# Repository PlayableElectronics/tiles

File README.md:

# PE - Tiles
Modular controller platform for midi, osc and more...

Connecting accessible components, well known standards (Grove, OSC, Midi) into easy and working systems tailored to your personal needs.

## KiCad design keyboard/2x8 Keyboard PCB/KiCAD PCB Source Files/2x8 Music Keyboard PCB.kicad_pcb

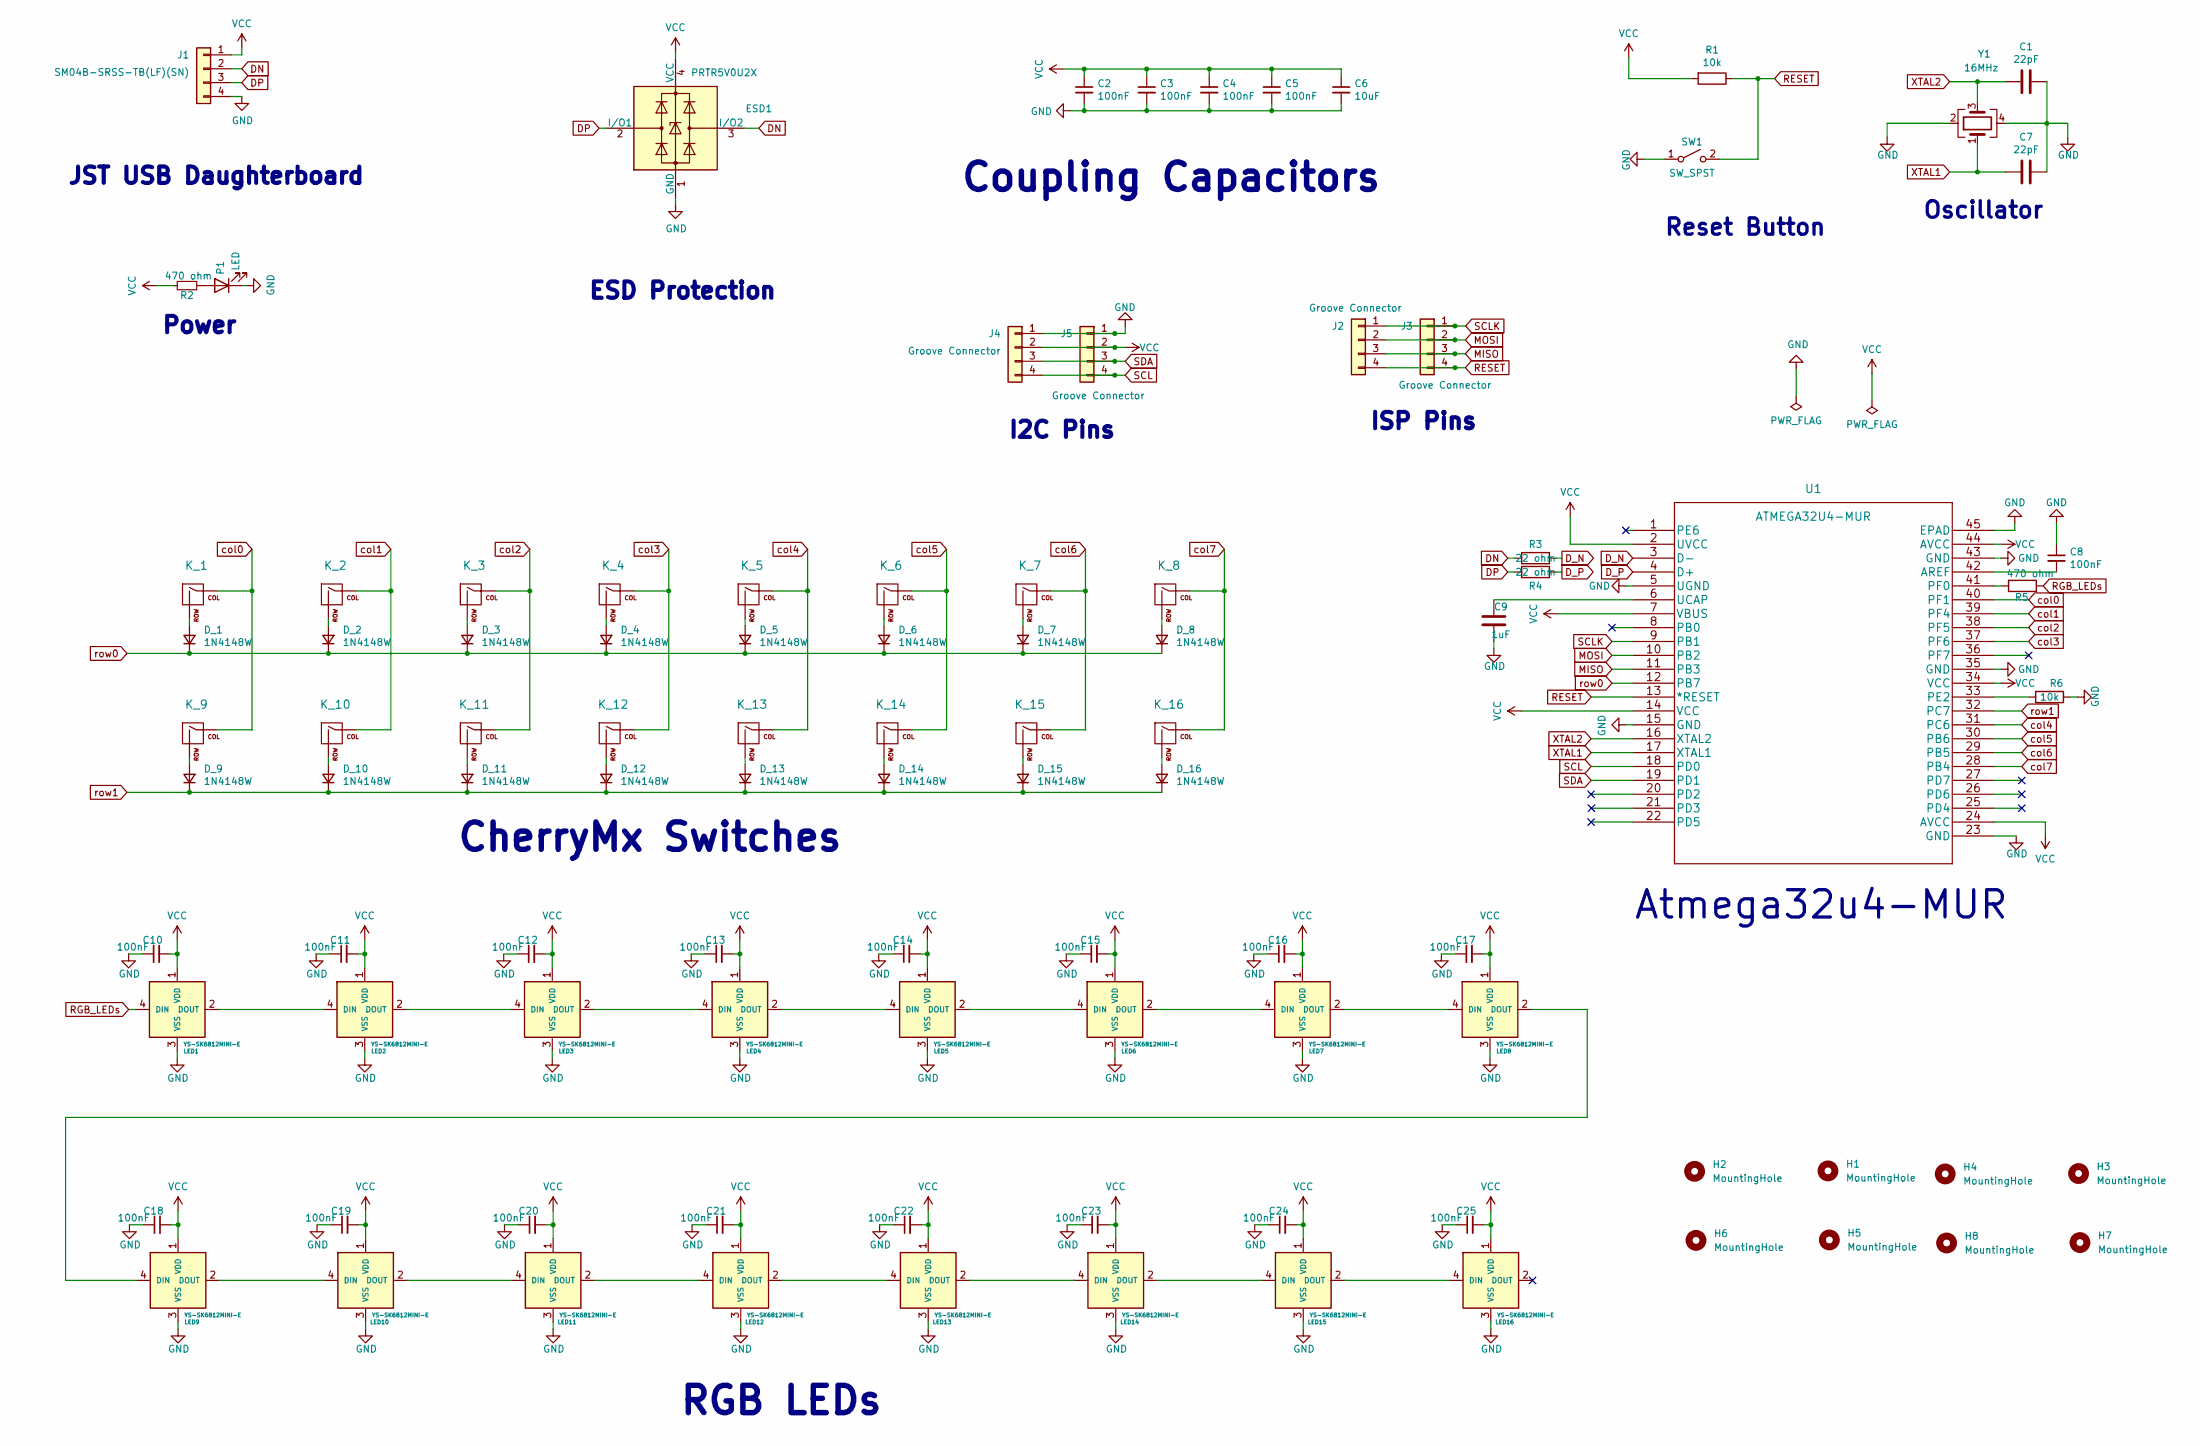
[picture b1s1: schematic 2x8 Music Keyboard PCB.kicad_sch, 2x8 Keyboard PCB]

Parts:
C1, C7: 22pF; C_0603_1608Metric
C2, C3, C4, C5, C8, C10, C11, C12, C13, C14, C15, C16, C17, C18, C19, C20, C21, C22, C23, C24, C25: 100nF; C_0603_1608Metric
C6: 10uF; C_0603_1608Metric
C9: 1uF; C_0603_1608Metric; LCSC Part # C28323
D_1, D_2, D_3, D_4, D_5, D_6, D_7, D_8, D_9, D_10, D_11, D_12, D_13, D_14, D_15, D_16: 1N4148W; D_SOD-123
ESD1: PRTR5V0U2X; LCSC C2827688
H1, H2, H3, H4, H5, H6, H7, H8: MountingHole; HOLE-3mm
J1: SM04B-SRSS-TB(LF)(SN); JST_SH_SM04B-SRSS-TB_1x04-1MP_P1.00mm_Horizontal
J2, J4: Groove Connector; JST_PH_S4B-PH-SM4-TB_1x04-1MP_P2.00mm_Horizontal
J3, J5: Groove Connector; JST_PH_B4B-PH-K_1x04_P2.00mm_Vertical
K_1, K_2, K_3, K_4, K_5, K_6, K_7, K_8, K_9, K_10, K_11, K_12, K_13, K_14, K_15, K_16: KEYSW-1u; MXOnly-1U-NoLED
LED1, LED2, LED3, LED4, LED5, LED6, LED7, LED8, LED9, LED10, LED11, LED12, LED13, LED14, LED15, LED16: YS-SK6812MINI-E; CRONE-SK6812MINI-E
P1: LED; LED_0603_1608Metric; LCSC C473820
R1, R6: 10k; R_0603_1608Metric; LCSC Part # C17414
R2, R5: 470 ohm; R_0603_1608Metric
R3, R4: 22 ohm; R_0603_1608Metric; LCSC Part # C17561
SW1: SW_SPST; K2-1187SQ-A4SW-06; Manufacturer Part Number K2-1187SQ-A4SW-06
U1: ATMEGA32U4-MUR; ATMEGA32U4-MURr; LCSC Part # C45874
Y1: 16MHz; Crystal_SMD_3225-4Pin_3.2x2.5mm; LCSC Part # C13738

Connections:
DN: ESD1.3 (I/O2), J1.2, R3.2
DP: ESD1.2 (I/O1), J1.3, R4.2
D_N: R3.1, U1.3 (D-)
D_P: R4.1, U1.4 (D+)
GND: C1.1, C2.2, C3.2, C4.2, C5.2, C6.2, C7.1, C8.1, C9.2, C10.1, C11.1, C12.1, C13.1, C14.1, C15.1, C16.1, C17.1, C18.1, C19.1, C20.1, C21.1, C22.1, C23.1, C24.1, C25.1, ESD1.1 (GND), J1.4, J4.1, J5.1, LED1.3 (VSS), LED2.3 (VSS), LED3.3 (VSS), LED4.3 (VSS), LED5.3 (VSS), LED6.3 (VSS), LED7.3 (VSS), LED8.3 (VSS), LED9.3 (VSS), LED10.3 (VSS), LED11.3 (VSS), LED12.3 (VSS), LED13.3 (VSS), LED14.3 (VSS), LED15.3 (VSS), LED16.3 (VSS), P1.1 (K), R6.1, SW1.1 (A), U1.5 (UGND), U1.15 (GND), U1.23 (GND), U1.35 (GND), U1.43 (GND), U1.45 (EPAD), Y1.2, Y1.4
MISO: J2.3, J3.3, U1.11 (PB3)
MOSI: J2.2, J3.2, U1.10 (PB2)
unnamed: C8.2, U1.42 (AREF)
unnamed: C9.1, U1.6 (UCAP)
unnamed: D_1.2 (A), K_1.2 (ROW)
unnamed: D_2.2 (A), K_2.2 (ROW)
unnamed: D_3.2 (A), K_3.2 (ROW)
unnamed: D_4.2 (A), K_4.2 (ROW)
unnamed: D_5.2 (A), K_5.2 (ROW)
unnamed: D_6.2 (A), K_6.2 (ROW)
unnamed: D_7.2 (A), K_7.2 (ROW)
unnamed: D_8.2 (A), K_8.2 (ROW)
unnamed: D_9.2 (A), K_9.2 (ROW)
unnamed: D_10.2 (A), K_10.2 (ROW)
unnamed: D_11.2 (A), K_11.2 (ROW)
unnamed: D_12.2 (A), K_12.2 (ROW)
unnamed: D_13.2 (A), K_13.2 (ROW)
unnamed: D_14.2 (A), K_14.2 (ROW)
unnamed: D_15.2 (A), K_15.2 (ROW)
unnamed: D_16.2 (A), K_16.2 (ROW)
unnamed: LED1.2 (DOUT), LED2.4 (DIN)
unnamed: LED2.2 (DOUT), LED3.4 (DIN)
unnamed: LED3.2 (DOUT), LED4.4 (DIN)
unnamed: LED4.2 (DOUT), LED5.4 (DIN)
unnamed: LED5.2 (DOUT), LED6.4 (DIN)
unnamed: LED6.2 (DOUT), LED7.4 (DIN)
unnamed: LED7.2 (DOUT), LED8.4 (DIN)
unnamed: LED8.2 (DOUT), LED9.4 (DIN)
unnamed: LED10.2 (DOUT), LED11.4 (DIN)
unnamed: LED9.2 (DOUT), LED10.4 (DIN)
unnamed: LED11.2 (DOUT), LED12.4 (DIN)
unnamed: LED12.2 (DOUT), LED13.4 (DIN)
unnamed: LED13.2 (DOUT), LED14.4 (DIN)
unnamed: LED14.2 (DOUT), LED15.4 (DIN)
unnamed: LED15.2 (DOUT), LED16.4 (DIN)
unnamed: P1.2 (A), R2.1
unnamed: R5.2, U1.41 (PF0)
unnamed: R6.2, U1.33 (PE2)
RESET: J2.4, J3.4, R1.1, SW1.2 (B), U1.13 (*RESET)
RGB_LEDs: LED1.4 (DIN), R5.1
SCL: J4.4, J5.4, U1.18 (PD0)
SCLK: J2.1, J3.1, U1.9 (PB1)
SDA: J4.3, J5.3, U1.19 (PD1)
VCC: C2.1, C3.1, C4.1, C5.1, C6.1, C10.2, C11.2, C12.2, C13.2, C14.2, C15.2, C16.2, C17.2, C18.2, C19.2, C20.2, C21.2, C22.2, C23.2, C24.2, C25.2, ESD1.4 (VCC), J1.1, J4.2, J5.2, LED1.1 (VDD), LED2.1 (VDD), LED3.1 (VDD), LED4.1 (VDD), LED5.1 (VDD), LED6.1 (VDD), LED7.1 (VDD), LED8.1 (VDD), LED9.1 (VDD), LED10.1 (VDD), LED11.1 (VDD), LED12.1 (VDD), LED13.1 (VDD), LED14.1 (VDD), LED15.1 (VDD), LED16.1 (VDD), R1.2, R2.2, U1.2 (UVCC), U1.7 (VBUS), U1.14 (VCC), U1.24 (AVCC), U1.34 (VCC), U1.44 (AVCC)
XTAL1: C7.2, U1.17 (XTAL1), Y1.1
XTAL2: C1.2, U1.16 (XTAL2), Y1.3
col0: K_1.1 (COL), K_9.1 (COL), U1.40 (PF1)
col1: K_2.1 (COL), K_10.1 (COL), U1.39 (PF4)
col2: K_3.1 (COL), K_11.1 (COL), U1.38 (PF5)
col3: K_4.1 (COL), K_12.1 (COL), U1.37 (PF6)
col4: K_5.1 (COL), K_13.1 (COL), U1.31 (PC6)
col5: K_6.1 (COL), K_14.1 (COL), U1.30 (PB6)
col6: K_7.1 (COL), K_15.1 (COL), U1.29 (PB5)
col7: K_8.1 (COL), K_16.1 (COL), U1.28 (PB4)
row0: D_1.1 (K), D_2.1 (K), D_3.1 (K), D_4.1 (K), D_5.1 (K), D_6.1 (K), D_7.1 (K), D_8.1 (K), U1.12 (PB7)
row1: D_9.1 (K), D_10.1 (K), D_11.1 (K), D_12.1 (K), D_13.1 (K), D_14.1 (K), D_15.1 (K), D_16.1 (K), U1.32 (PC7)

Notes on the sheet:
Power
RGB LEDs
JST USB Daughterboard
Oscillator
CherryMx Switches
ESD Protection
Coupling Capacitors
Atmega32u4-MUR
ISP Pins
I2C Pins
Reset Button

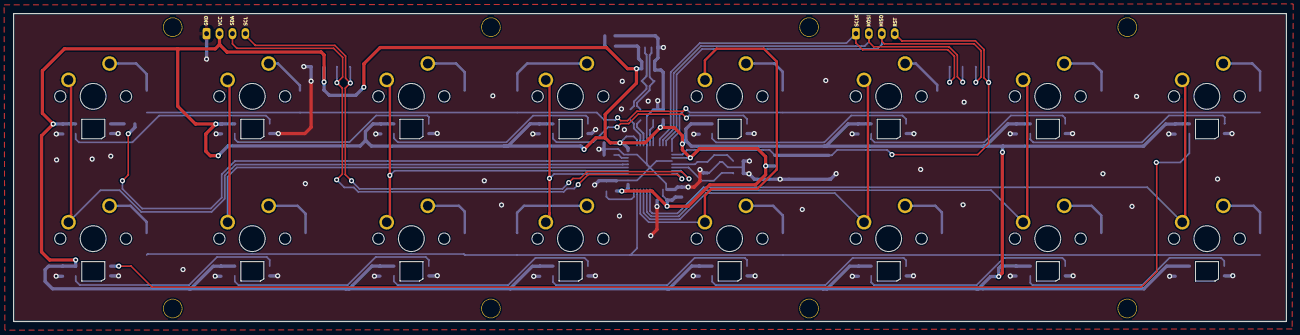
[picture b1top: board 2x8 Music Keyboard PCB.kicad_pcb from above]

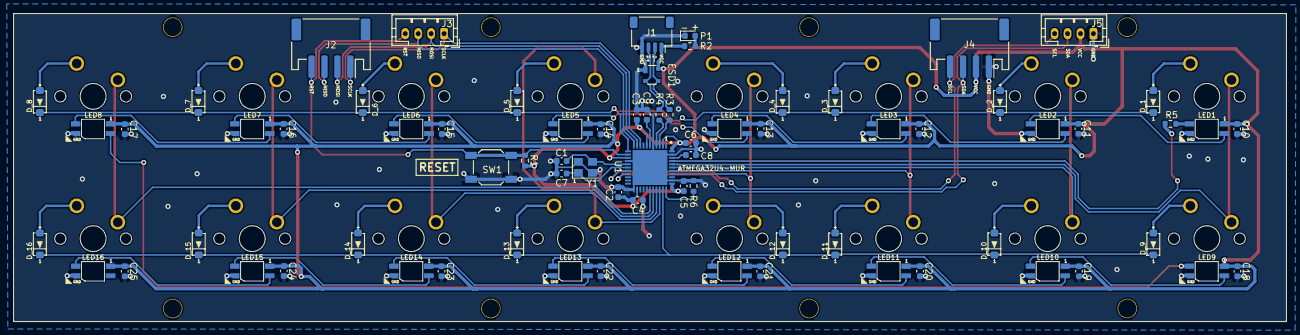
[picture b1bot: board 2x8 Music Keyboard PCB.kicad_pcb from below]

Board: 2 copper layers, 196.8 x 47.6 mm, 97 parts (77 on the bottom side), 61 nets.

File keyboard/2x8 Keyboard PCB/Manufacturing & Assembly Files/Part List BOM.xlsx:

Item | Qty | Reference(s) | Value | Footprint | JLCPCB Part# | Weblink | Column1 | Column2
1 | 2 | C1, C7 | 22pF | Ahsan Libs:C_0603_1608Metric | C1653 | https://lcsc.com/product-detail/Multilayer-Ceramic-Capacitor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
2 | 21 | C2, C3, C4, C5, C8, C10, C11, C12, C13, C14, C15, C16, C17, C18, C19, C20, C21,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 | 100nF | Ahsan Libs:C_0603_1608Metric | C14663 | https://lcsc.com/product-detail/Multilayer-Ceramic-Capacitor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
3 | 1 | C6 | 10uF | Ahsan Libs:C_0603_1608Metric | C15849 | https://lcsc.com/product-detail/Multilayer-Ceramic-Capacitor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
4 | 1 | C9 | 1uF | Ahsan Libs:C_0603_1608Metric | C96446 | https://www.lcsc.com/product-detail/Multilayer-Ceramic-Capac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
5 | 16 | D_1, D_2, D_3, D_4, D_5, D_6, D_7, D_8, D_9, D_10, D_11, D_12, D_13, D_14, D_15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 | 1N4148W | Ahsan Libs:D_SOD-123 | C81598 | https://lcsc.com/product-detail/Switching-Diode_ST-Semtech-1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
6 | 1 | ESD1 | PRTR5V0U2X | Ahsan Libs:PRTR5V0U2X | C2827688 | https://www.lcsc.com/product-detail/ESD-Protection-Devices_T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
7 | 1 | J1 | SM04B-SRSS-TB(LF)(SN) | Ahsan Libs:JST_SH_SM04B-SRSS-TB_1x04-1MP_P1.00mm_Horizontal | C160404 | https://www.lcsc.com/product-detail/Others_JST-Sales-America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
8 | 2 | J2, J4 | Groove Connector | Connector_JST:JST_PH_S4B-PH-SM4-TB_1x04-1MP_P2.00mm_Horizontal | C265289 | https://www.lcsc.com/product-detail/Wire-To-Board-Wire-To-Wi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
9 | 2 | J3, J5 | Groove Connector | Connector_JST:JST_PH_B4B-PH-K_1x04_P2.00mm_Vertical | C131334 | https://www.lcsc.com/product-detail/Wire-To-Board-Wire-To-Wi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
10 | 16 | K_1, K_2, K_3, K_4, K_5, K_6, K_7, K_8, K_9, K_10, K_11, K_12, K_13, K_14, K_15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 | KEYSW-1u | Ahsan Libs:MXOnly-1U-NoLED | C400232 | https://www.lcsc.com/product-detail/Mechanical-Keyboard-Shaf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
11 | 16 | LED1, LED2, LED3, LED4, LED5, LED6, LED7, LED8, LED9, LED10, LED11, LED12, LED1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 | YS-SK6812MINI-E | Ahsan Libs:CRONE-SK6812MINI-E | C5149201 | https://www.lcsc.com/product-detail/Light-Emitting-Diodes-LE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 | https://shop.beekeeb.com/product/sk6812mini-e/ | https://www.adafruit.com/product/4960
12 | 1 | P1 | LED | Ahsan Libs:LED_0603_1608Metric | C72041 | https://lcsc.com/product-detail/Light-Emitting-Diodes-LED_Ev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
13 | 2 | R1, R6 | 10k | Ahsan Libs:R_0603_1608Metric | C25804 | https://lcsc.com/product-detail/Chip-Resistor-Surface-Mount_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
14 | 1 | R2 | 470 ohm | Ahsan Libs:R_0603_1608Metric | C23179 | https://lcsc.com/product-detail/Chip-Resistor-Surface-Mount_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
15 | 2 | R3, R4 | 22 ohm | Ahsan Libs:R_0603_1608Metric | C1203 | https://lcsc.com/product-detail/Chip-Resistor-Surface-Mount_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
16 | 1 | R5 | 470 ohm | Ahsan Libs:R_0603_1608Metric | C23179 | https://lcsc.com/product-detail/Chip-Resistor-Surface-Mount_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
17 | 1 | SW1 | SW_SPST | Ahsan Libs:K2-1187SQ-A4SW-06 | C388295 | https://lcsc.com/product-detail/Tactile-Switches_SHOU-HAN-TS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
18 | 1 | U1 | ATMEGA32U4-MUR | Ahsan Libs:ATMEGA32U4-MURr | C112161 | https://lcsc.com/product-detail/ATMEL-AVR_Microchip-Tech-ATM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
19 | 1 | Y1 | 16MHz | Ahsan Libs:Crystal_SMD_3225-4Pin_3.2x2.5mm | C13738 | https://lcsc.com/product-detail/Crystals_Yangxing-Tech-X3225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

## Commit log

2023-01-13 init
2023-01-15 added keyboard tile pcb and few scad files
